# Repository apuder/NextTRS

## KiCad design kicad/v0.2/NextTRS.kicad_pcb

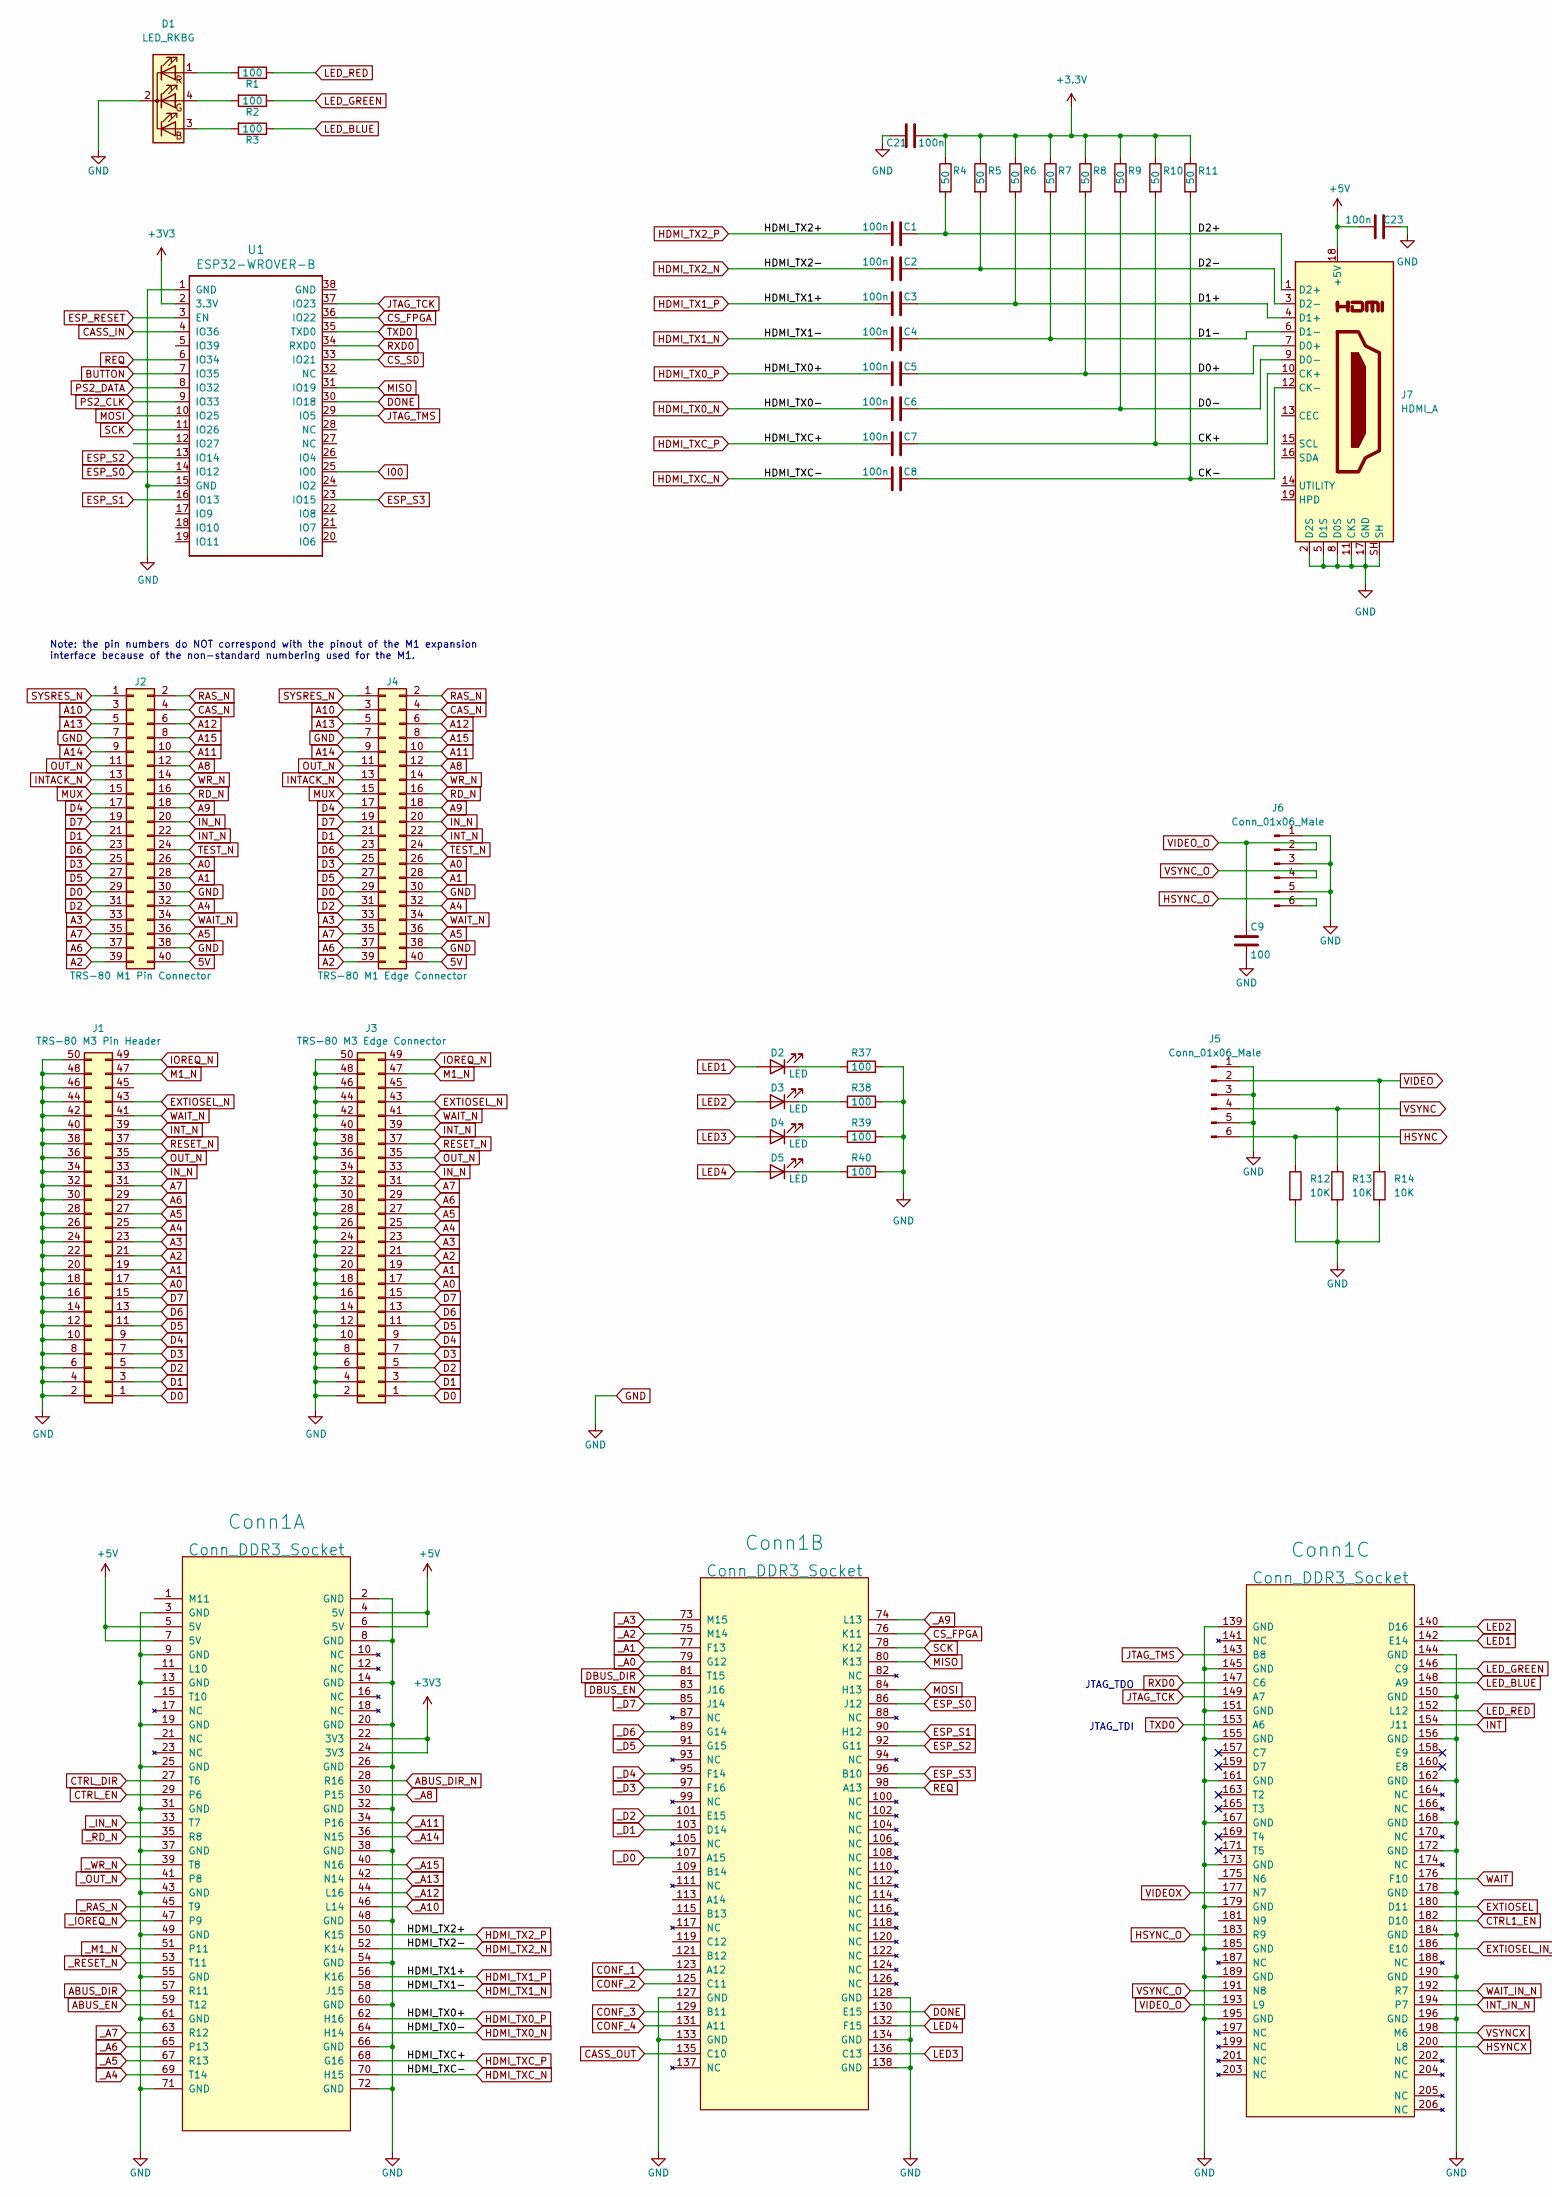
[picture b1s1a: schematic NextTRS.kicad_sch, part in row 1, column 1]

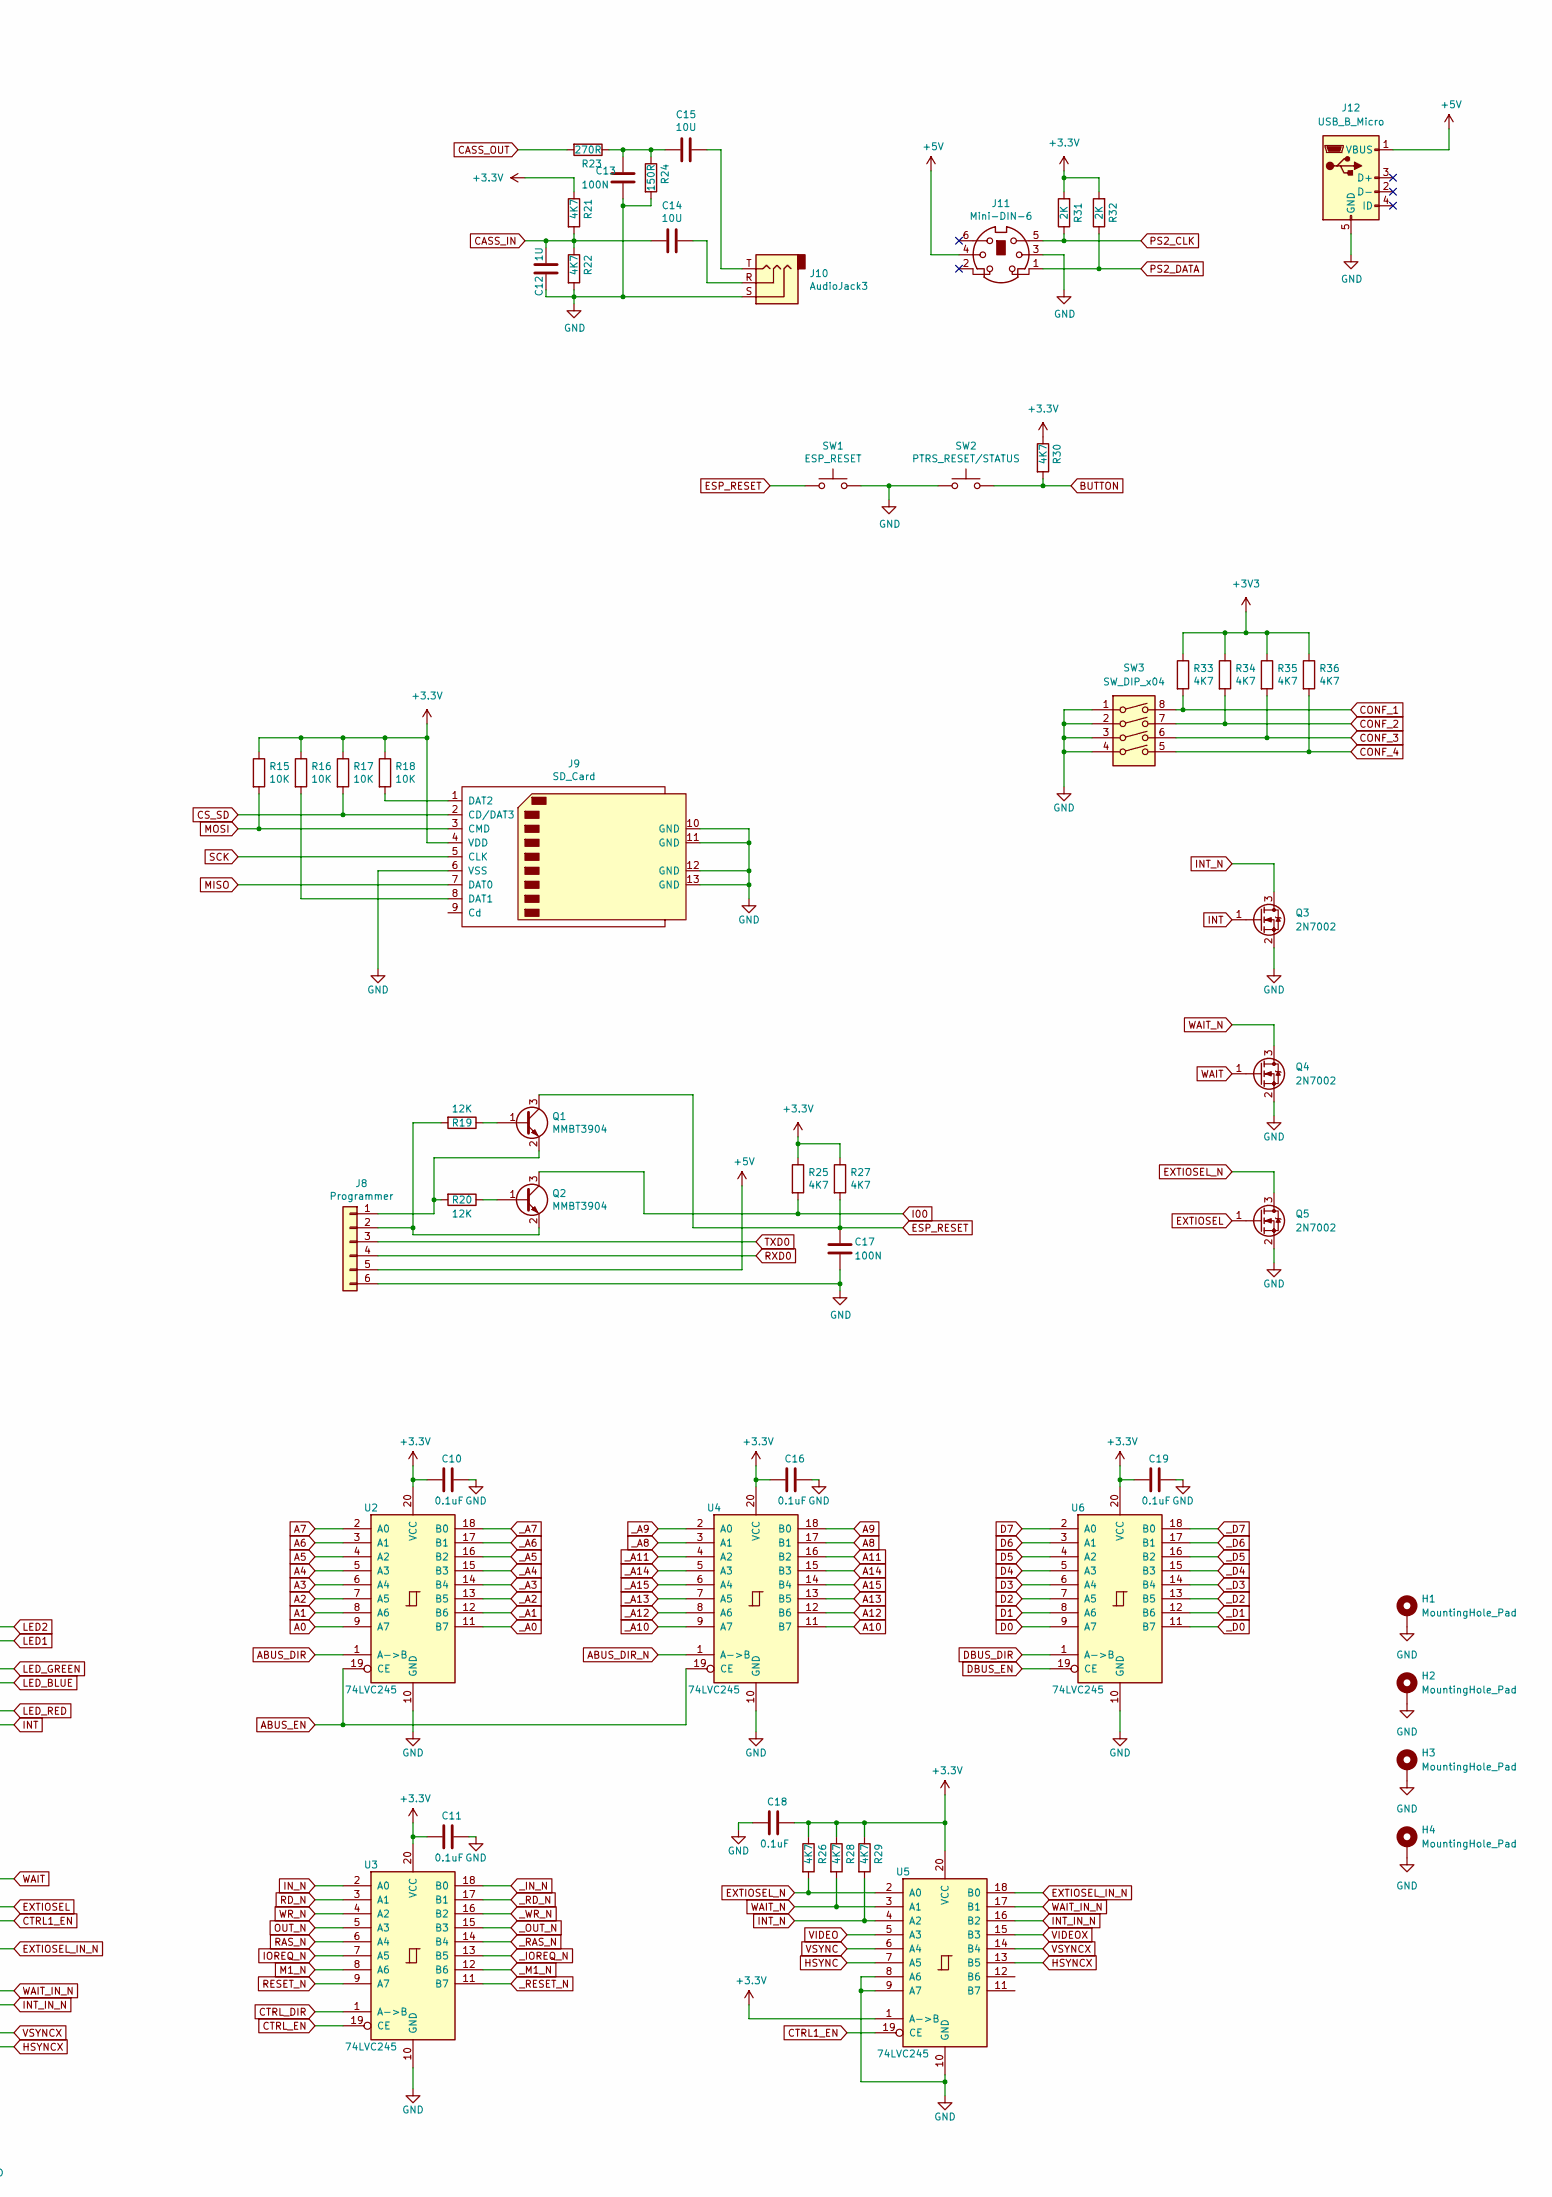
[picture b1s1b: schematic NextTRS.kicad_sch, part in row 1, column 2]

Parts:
C1, C2, C3, C4, C5, C6, C7, C8, C21, C23: 100n; C_0805_2012Metric_Pad1.18x1.45mm_HandSolder
C9: 100; C_0805_2012Metric_Pad1.18x1.45mm_HandSolder
C10, C11, C16, C18, C19: 0.1uF; C_0805_2012Metric_Pad1.18x1.45mm_HandSolder
C12: 1U; C_1206_3216Metric_Pad1.33x1.80mm_HandSolder
C13, C17: 100N; C_0805_2012Metric_Pad1.18x1.45mm_HandSolder
C14, C15: 10U; C_1206_3216Metric_Pad1.33x1.80mm_HandSolder
Conn1: Conn_DDR3_Socket; DDR3_socket
D1: LED_RKBG; LED_D5.0mm-4_RGB
D2, D3, D4, D5: LED; LED_0805_2012Metric_Pad1.15x1.40mm_HandSolder
H1, H2, H3, H4: MountingHole_Pad; MountingHole_3mm_Pad_Via
J1: TRS-80 M3 Pin Header; PinHeader_2x25_P2.54mm_Vertical
J2: TRS-80 M1 Pin Connector; PinHeader_2x20_P2.54mm_Vertical
J3: TRS-80 M3 Edge Connector; EDGE50
J4: TRS-80 M1 Edge Connector; TRSEDGE
J5, J6: Conn_01x06_Male; PinHeader_1x06_P2.54mm_Horizontal
J7: HDMI_A; HDMI_A_Molex_208658-1001_Horizontal
J8: Programmer; PinSocket_1x06_P2.54mm_Vertical
J9: SD_Card; TFP09-2-12B
J10: AudioJack3; Jack_3.5mm_CUI_SJ1-3535NG_Horizontal_CircularHoles
J11: Mini-DIN-6; minidin_6_ps2_pcb_mount
J12: USB_B_Micro; USBmicro-B
Q1, Q2: MMBT3904; SOT-23
Q3, Q4, Q5: 2N7002; SOT-23
R1, R2, R3, R37, R38, R39, R40: 100; R_0805_2012Metric_Pad1.20x1.40mm_HandSolder
R4, R5, R6, R7, R8, R9, R10, R11: 50; R_0805_2012Metric_Pad1.20x1.40mm_HandSolder
R12, R13, R14, R15, R16, R17, R18: 10K; R_0805_2012Metric_Pad1.20x1.40mm_HandSolder
R19, R20: 12K; R_0805_2012Metric_Pad1.20x1.40mm_HandSolder
R21, R22, R25, R26, R27, R28, R29, R30, R33, R34, R35, R36: 4K7; R_0805_2012Metric_Pad1.20x1.40mm_HandSolder
R23: 270R; R_0805_2012Metric_Pad1.20x1.40mm_HandSolder
R24: 150R; R_0805_2012Metric_Pad1.20x1.40mm_HandSolder
R31, R32: 2K; R_0805_2012Metric_Pad1.20x1.40mm_HandSolder
SW1: ESP_RESET; SW_PUSH_6mm
SW2: PTRS_RESET/STATUS; SW_PUSH_6mm
SW3: SW_DIP_x04; SW_DIP_SPSTx04_Slide_6.7x11.72mm_W8.61mm_P2.54mm_LowProfile
U1: ESP32-WROVER-B; ESP32-WROVER
U2, U3, U4, U5, U6: 74LVC245; SSOP-20_5.3x7.2mm_P0.65mm_slim

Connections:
5V: J2.40, J4.40
+5V: C23.1, Conn1.4 (5V), Conn1.5 (5V), Conn1.6 (5V), Conn1.7 (5V), J7.18 (+5V), J8.5, J11.4, J12.1 (VBUS)
/CK+: C7.2, J7.10 (CK+), R10.2
/CK-: C8.2, J7.12 (CK-), R11.2
/D0+: C5.2, J7.7 (D0+), R8.2
/D0-: C6.2, J7.9 (D0-), R9.2
/D1+: C3.2, J7.4 (D1+), R6.2
/D1-: C4.2, J7.6 (D1-), R7.2
/D2+: C1.2, J7.1 (D2+), R4.2
/D2-: C2.2, J7.3 (D2-), R5.2
A0: J1.17, J2.26, J3.17, J4.26, U2.9 (A7)
A1: J1.19, J2.28, J3.19, J4.28, U2.8 (A6)
A2: J1.21, J2.39, J3.21, J4.39, U2.7 (A5)
A3: J1.23, J2.33, J3.23, J4.33, U2.6 (A4)
A4: J1.25, J2.32, J3.25, J4.32, U2.5 (A3)
A5: J1.27, J2.36, J3.27, J4.36, U2.4 (A2)
A6: J1.29, J2.37, J3.29, J4.37, U2.3 (A1)
A7: J1.31, J2.35, J3.31, J4.35, U2.2 (A0)
A8: J2.12, J4.12, U4.17 (B1)
A9: J2.18, J4.18, U4.18 (B0)
A10: J2.3, J4.3, U4.11 (B7)
A11: J2.10, J4.10, U4.16 (B2)
A12: J2.6, J4.6, U4.12 (B6)
A13: J2.5, J4.5, U4.13 (B5)
A14: J2.9, J4.9, U4.15 (B3)
A15: J2.8, J4.8, U4.14 (B4)
ABUS_DIR: Conn1.57 (R11), U2.1 (A->B)
ABUS_DIR_N: Conn1.28 (R16), U4.1 (A->B)
ABUS_EN: Conn1.59 (T12), U2.19 (CE), U4.19 (CE)
BUTTON: R30.2, SW2.2, U1.7 (IO35)
CASS_IN: C12.1, C14.2, R21.2, R22.1, U1.4 (IO36)
CASS_OUT: Conn1.135 (C10), R23.2
CAS_N: J2.4, J4.4
CONF_1: Conn1.123 (A12), R33.2, SW3.8
CONF_2: Conn1.125 (C11), R34.2, SW3.7
CONF_3: Conn1.129 (B11), R35.2, SW3.6
CONF_4: Conn1.131 (A11), R36.2, SW3.5
CS_FPGA: Conn1.76 (K11), U1.36 (IO22)
CS_SD: J9.2 (CD/DAT3), R17.2, U1.33 (IO21)
CTRL1_EN: Conn1.182 (D10), U5.19 (CE)
CTRL_DIR: Conn1.27 (T6), U3.1 (A->B)
CTRL_EN: Conn1.29 (P6), U3.19 (CE)
D0: J1.1, J2.29, J3.1, J4.29, U6.9 (A7)
D1: J1.3, J2.21, J3.3, J4.21, U6.8 (A6)
D2: J1.5, J2.31, J3.5, J4.31, U6.7 (A5)
D3: J1.7, J2.25, J3.7, J4.25, U6.6 (A4)
D4: J1.9, J2.17, J3.9, J4.17, U6.5 (A3)
D5: J1.11, J2.27, J3.11, J4.27, U6.4 (A2)
D6: J1.13, J2.23, J3.13, J4.23, U6.3 (A1)
D7: J1.15, J2.19, J3.15, J4.19, U6.2 (A0)
DBUS_DIR: Conn1.81 (T15), U6.1 (A->B)
DBUS_EN: Conn1.83 (J16), U6.19 (CE)
DONE: Conn1.130 (E15), U1.30 (IO18)
ESP_RESET: C17.1, Q1.3 (C), R27.2, SW1.1, U1.3 (EN)
ESP_S0: Conn1.86 (J12), U1.14 (IO12)
ESP_S1: Conn1.90 (H12), U1.16 (IO13)
ESP_S2: Conn1.92 (G11), U1.13 (IO14)
ESP_S3: Conn1.96 (B10), U1.23 (IO15)
EXTIOSEL: Conn1.180 (D11), Q5.1 (G)
EXTIOSEL_IN_N: Conn1.186 (E10), U5.18 (B0)
EXTIOSEL_N: J1.43, J3.43, Q5.3 (D), R26.2, U5.2 (A0)
GND: C9.2, C10.1, C11.1, C12.2, C13.2, C16.1, C17.2, C18.2, C19.1, C21.2, C23.2, Conn1.2 (GND), Conn1.3 (GND), Conn1.8 (GND), Conn1.9 (GND), Conn1.13 (GND), Conn1.14 (GND), Conn1.19 (GND), Conn1.20 (GND), Conn1.25 (GND), Conn1.26 (GND), Conn1.31 (GND), Conn1.32 (GND), Conn1.37 (GND), Conn1.38 (GND), Conn1.43 (GND), Conn1.48 (GND), Conn1.49 (GND), Conn1.54 (GND), Conn1.55 (GND), Conn1.60 (GND), Conn1.61 (GND), Conn1.66 (GND), Conn1.71 (GND), Conn1.72 (GND), Conn1.127 (GND), Conn1.128 (GND), Conn1.133 (GND), Conn1.134 (GND), Conn1.138 (GND), Conn1.139 (GND), Conn1.144 (GND), Conn1.145 (GND), Conn1.150 (GND), Conn1.151 (GND), Conn1.155 (GND), Conn1.156 (GND), Conn1.161 (GND), Conn1.162 (GND), Conn1.167 (GND), Conn1.168 (GND), Conn1.172 (GND), Conn1.173 (GND), Conn1.178 (GND), Conn1.179 (GND), Conn1.184 (GND), Conn1.185 (GND), Conn1.189 (GND), Conn1.190 (GND), Conn1.195 (GND), Conn1.196 (GND), D1.2 (K), H1.1, H2.1, H3.1, H4.1, J1.2, J1.4, J1.6, J1.8, J1.10, J1.12, J1.14, J1.16, J1.18, J1.20, J1.22, J1.24, J1.26, J1.28, J1.30, J1.32, J1.34, J1.36, J1.38, J1.40, J1.42, J1.44, J1.46, J1.48, J1.50, J2.7, J2.30, J2.38, J3.2, J3.4, J3.6, J3.8, J3.10, J3.12, J3.14, J3.16, J3.18, J3.20, J3.22, J3.24, J3.26, J3.28, J3.30, J3.32, J3.34, J3.36, J3.38, J3.40, J3.42, J3.44, J3.46, J3.48, J3.50, J4.7, J4.30, J4.38, J5.1, J5.3, J5.5, J6.1, J6.3, J6.5, J7.2 (D2S), J7.5 (D1S), J7.8 (D0S), J7.11 (CKS), J7.17 (GND), J7.SH, J8.6, J9.6 (VSS), J9.10 (GND), J9.11 (GND), J9.12 (GND), J9.13 (GND), J10.S, J11.3, J12.5 (GND), Q3.2 (S), Q4.2 (S), Q5.2 (S), R12.2, R13.2, R14.2, R22.2, R24.2, R37.2, R38.2, R39.2, R40.2, SW1.2, SW2.1, SW3.1, SW3.2, SW3.3, SW3.4, U1.1 (GND), U1.15 (GND), U2.10 (GND), U3.10 (GND), U4.10 (GND), U5.8 (A6), U5.9 (A7), U5.10 (GND), U6.10 (GND)
HDMI_TX0_N: C6.1, Conn1.64 (H14)
HDMI_TX0_P: C5.1, Conn1.62 (H16)
HDMI_TX1_N: C4.1, Conn1.58 (J15)
HDMI_TX1_P: C3.1, Conn1.56 (K16)
HDMI_TX2_N: C2.1, Conn1.52 (K14)
HDMI_TX2_P: C1.1, Conn1.50 (K15)
HDMI_TXC_N: C8.1, Conn1.70 (H15)
HDMI_TXC_P: C7.1, Conn1.68 (G16)
HSYNC: J5.6, R12.1, U5.7 (A5)
HSYNCX: Conn1.200 (L8), U5.13 (B5)
HSYNC_O: Conn1.183 (R9), J6.6
I00: Q2.3 (C), R25.2, U1.25 (IO0)
INT: Conn1.154 (J11), Q3.1 (G)
INTACK_N: J2.13, J4.13
INT_IN_N: Conn1.194 (P7), U5.16 (B2)
INT_N: J1.39, J2.22, J3.39, J4.22, Q3.3 (D), R29.2, U5.4 (A2)
IN_N: J1.33, J2.20, J3.33, J4.20, U3.2 (A0)
IOREQ_N: J1.49, J3.49, U3.7 (A5)
JTAG_TCK: Conn1.149 (A7), U1.37 (IO23)
JTAG_TMS: Conn1.143 (B8), U1.29 (IO5)
LED1: Conn1.142 (E14), D2.2 (A)
LED2: Conn1.140 (D16), D3.2 (A)
LED3: Conn1.136 (C13), D4.2 (A)
LED4: Conn1.132 (F15), D5.2 (A)
LED_BLUE: Conn1.148 (A9), R3.1
LED_GREEN: Conn1.146 (C9), R2.1
LED_RED: Conn1.152 (L12), R1.1
M1_N: J1.47, J3.47, U3.8 (A6)
MISO: Conn1.80 (K13), J9.7 (DAT0), U1.31 (IO19)
MOSI: Conn1.84 (H13), J9.3 (CMD), R15.2, U1.10 (IO25)
MUX: J2.15, J4.15
unnamed: C13.1, C15.2, R23.1, R24.1
unnamed: C14.1, J10.R
unnamed: C15.1, J10.T
unnamed: D1.1 (RA), R1.2
unnamed: D1.3 (BA), R3.2
unnamed: D1.4 (GA), R2.2
unnamed: D2.1 (K), R37.1
unnamed: D3.1 (K), R38.1
unnamed: D4.1 (K), R39.1
unnamed: D5.1 (K), R40.1
unnamed: J8.1, Q1.2 (E), R20.2
unnamed: J8.2, Q2.2 (E), R19.2
unnamed: J9.1 (DAT2), R18.2
unnamed: J9.8 (DAT1), R16.2
unnamed: Q1.1 (B), R19.1
unnamed: Q2.1 (B), R20.1
OUT_N: J1.35, J2.11, J3.35, J4.11, U3.5 (A3)
PS2_CLK: J11.5, R31.1, U1.9 (IO33)
PS2_DATA: J11.1, R32.1, U1.8 (IO32)
RAS_N: J2.2, J4.2, U3.6 (A4)
RD_N: J2.16, J4.16, U3.3 (A1)
REQ: Conn1.98 (A13), U1.6 (IO34)
RESET_N: J1.37, J3.37, U3.9 (A7)
RXD0: Conn1.147 (C6), J8.4, U1.34 (RXD0)
SCK: Conn1.78 (K12), J9.5 (CLK), U1.11 (IO26)
SYSRES_N: J2.1, J4.1
TEST_N: J2.24, J4.24
TXD0: Conn1.153 (A6), J8.3, U1.35 (TXD0)
VIDEO: J5.2, R14.1, U5.5 (A3)
VIDEOX: Conn1.177 (N7), U5.15 (B3)
VIDEO_O: C9.1, Conn1.193 (L9), J6.2
VSYNC: J5.4, R13.1, U5.6 (A4)
VSYNCX: Conn1.198 (M6), U5.14 (B4)
VSYNC_O: Conn1.191 (N8), J6.4
WAIT: Conn1.176 (F10), Q4.1 (G)
WAIT_IN_N: Conn1.192 (R7), U5.17 (B1)
WAIT_N: J1.41, J2.34, J3.41, J4.34, Q4.3 (D), R28.2, U5.3 (A1)
WR_N: J2.14, J4.14, U3.4 (A2)
_A0: Conn1.79 (G12), U2.11 (B7)
_A1: Conn1.77 (F13), U2.12 (B6)
_A2: Conn1.75 (M14), U2.13 (B5)
_A3: Conn1.73 (M15), U2.14 (B4)
_A4: Conn1.69 (T14), U2.15 (B3)
_A5: Conn1.67 (R13), U2.16 (B2)
_A6: Conn1.65 (P13), U2.17 (B1)
_A7: Conn1.63 (R12), U2.18 (B0)
_A8: Conn1.30 (P15), U4.3 (A1)
_A9: Conn1.74 (L13), U4.2 (A0)
_A10: Conn1.46 (L14), U4.9 (A7)
_A11: Conn1.34 (P16), U4.4 (A2)
_A12: Conn1.44 (L16), U4.8 (A6)
_A13: Conn1.42 (N14), U4.7 (A5)
_A14: Conn1.36 (N15), U4.5 (A3)
_A15: Conn1.40 (N16), U4.6 (A4)
_D0: Conn1.107 (A15), U6.11 (B7)
_D1: Conn1.103 (D14), U6.12 (B6)
_D2: Conn1.101 (E15), U6.13 (B5)
_D3: Conn1.97 (F16), U6.14 (B4)
_D4: Conn1.95 (F14), U6.15 (B3)
_D5: Conn1.91 (G15), U6.16 (B2)
_D6: Conn1.89 (G14), U6.17 (B1)
_D7: Conn1.85 (J14), U6.18 (B0)
_IN_N: Conn1.33 (T7), U3.18 (B0)
_IOREQ_N: Conn1.47 (P9), U3.13 (B5)
_M1_N: Conn1.51 (P11), U3.12 (B6)
_OUT_N: Conn1.41 (P8), U3.15 (B3)
_RAS_N: Conn1.45 (T9), U3.14 (B4)
_RD_N: Conn1.35 (R8), U3.17 (B1)
_RESET_N: Conn1.53 (T11), U3.11 (B7)
_WR_N: Conn1.39 (T8), U3.16 (B2)

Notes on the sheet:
JTAG_TDO
Note: the pin numbers do NOT correspond with the pinout of the M1 expansion interface because of the non-standard numbering used for the M1.
JTAG_TDI

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
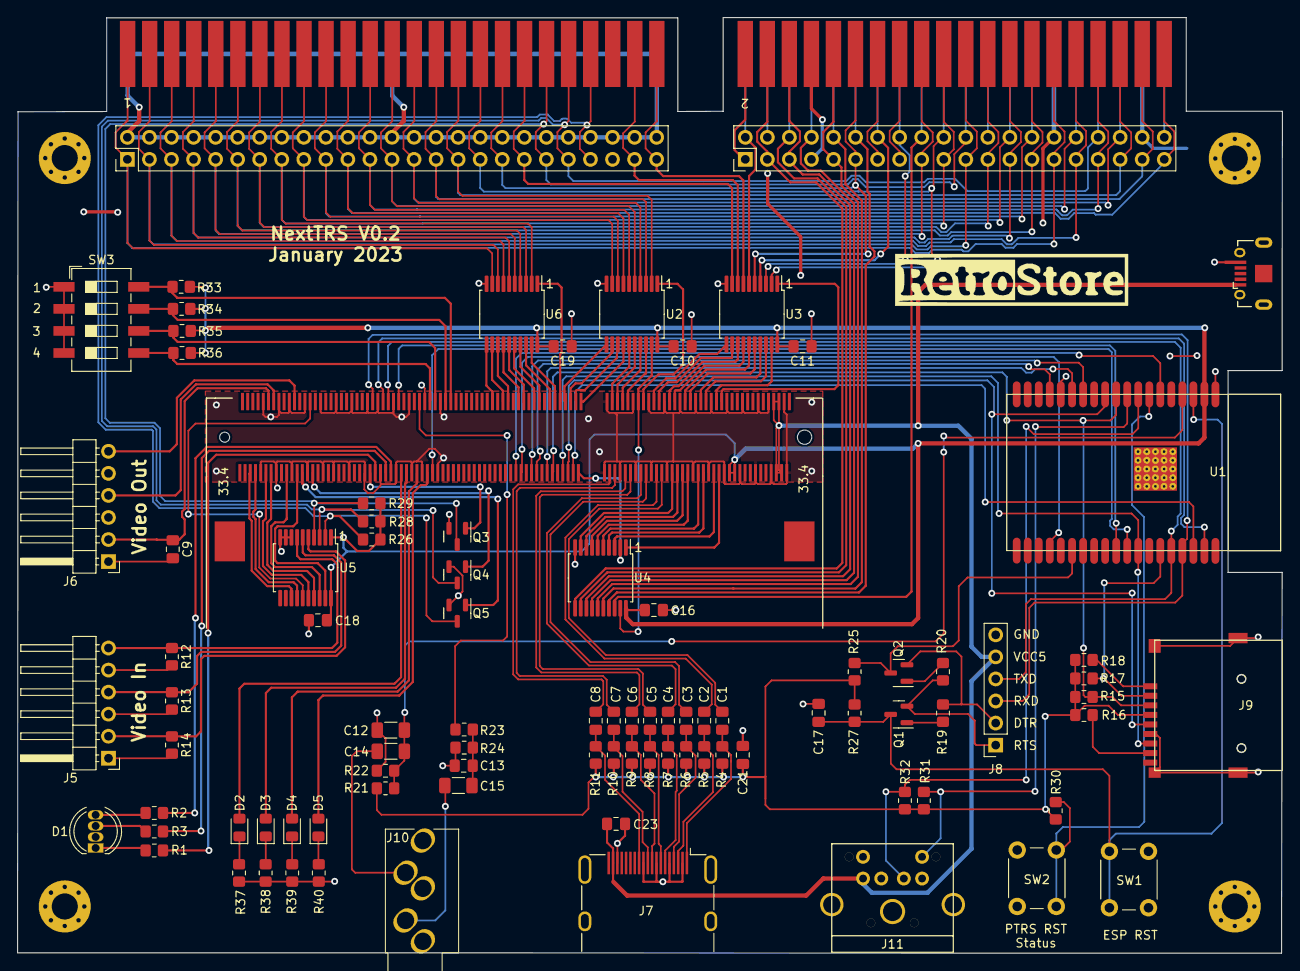
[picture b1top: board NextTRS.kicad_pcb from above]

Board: 2 copper layers, 145.7 x 107.8 mm, 98 parts (0 on the bottom side), 165 nets.

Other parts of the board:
G1: LOGO

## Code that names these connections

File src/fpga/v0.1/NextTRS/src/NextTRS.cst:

//Copyright (C)2014-2022 Gowin Semiconductor Corporation.
//All rights reserved. 
//File Title: Physical Constraints file
//GOWIN Version: 1.9.8.09
//Part Number: GW2A-LV18PG256C8/I7
//Device: GW2A-18C
//Created Time: Tue 12 27 23:20:03 2022

IO_LOC "CTRL1_EN" D10;
IO_PORT "CTRL1_EN" PULL_MODE=UP DRIVE=8;
IO_LOC "EXTIOSEL" D11;
IO_PORT "EXTIOSEL" PULL_MODE=UP DRIVE=8;
IO_LOC "WAIT" F10;
IO_PORT "WAIT" PULL_MODE=UP DRIVE=8;
IO_LOC "INT" J11;
IO_PORT "INT" PULL_MODE=UP DRIVE=8;
IO_LOC "LED_BLUE" A9;
IO_PORT "LED_BLUE" PULL_MODE=UP DRIVE=8;
IO_LOC "LED_RED" L12;
IO_PORT "LED_RED" PULL_MODE=UP DRIVE=8;
IO_LOC "LED_GREEN" C9;
IO_PORT "LED_GREEN" PULL_MODE=UP DRIVE=8;
IO_LOC "VIDEO_O" L9;
IO_PORT "VIDEO_O" PULL_MODE=UP DRIVE=8;
IO_LOC "VSYNC_O" N8;
IO_PORT "VSYNC_O" PULL_MODE=UP DRIVE=8;
IO_LOC "HSYNC_O" R9;
IO_PORT "HSYNC_O" PULL_MODE=UP DRIVE=8;
IO_LOC "LED[3]" F15;
IO_PORT "LED[3]" PULL_MODE=UP DRIVE=8;
IO_LOC "LED[2]" C13;
IO_PORT "LED[2]" PULL_MODE=UP DRIVE=8;
IO_LOC "LED[1]" D16;
IO_PORT "LED[1]" PULL_MODE=UP DRIVE=8;
IO_LOC "LED[0]" E14;
IO_PORT "LED[0]" PULL_MODE=UP DRIVE=8;
IO_LOC "REQ" A13;
IO_PORT "REQ" PULL_MODE=UP DRIVE=8;
IO_LOC "ESP_S[3]" B10;
IO_PORT "ESP_S[3]" PULL_MODE=UP DRIVE=8;
IO_LOC "ESP_S[2]" G11;
IO_PORT "ESP_S[2]" PULL_MODE=UP DRIVE=8;
IO_LOC "ESP_S[1]" H12;
IO_PORT "ESP_S[1]" PULL_MODE=UP DRIVE=8;
IO_LOC "ESP_S[0]" J12;
IO_PORT "ESP_S[0]" PULL_MODE=UP DRIVE=8;
IO_LOC "MISO" K13;
IO_PORT "MISO" PULL_MODE=UP DRIVE=8;
IO_LOC "CASS_OUT" C10;
IO_PORT "CASS_OUT" PULL_MODE=UP DRIVE=8;
IO_LOC "DBUS_EN" J16;
IO_PORT "DBUS_EN" PULL_MODE=UP DRIVE=8;
IO_LOC "DBUS_DIR" T15;
IO_PORT "DBUS_DIR" PULL_MODE=UP DRIVE=8;
IO_LOC "HDMI_TXC_N" H15;
IO_PORT "HDMI_TXC_N" PULL_MODE=UP DRIVE=8;
IO_LOC "HDMI_TXC_P" G16;
IO_PORT "HDMI_TXC_P" PULL_MODE=UP DRIVE=8;
IO_LOC "HDMI_TX_N[2]" K14;
IO_PORT "HDMI_TX_N[2]" PULL_MODE=UP DRIVE=8;
IO_LOC "HDMI_TX_N[1]" J15;
IO_PORT "HDMI_TX_N[1]" PULL_MODE=UP DRIVE=8;
IO_LOC "HDMI_TX_N[0]" H14;
IO_PORT "HDMI_TX_N[0]" PULL_MODE=UP DRIVE=8;
IO_LOC "HDMI_TX_P[2]" K15;
IO_PORT "HDMI_TX_P[2]" PULL_MODE=UP DRIVE=8;
IO_LOC "HDMI_TX_P[1]" K16;
IO_PORT "HDMI_TX_P[1]" PULL_MODE=UP DRIVE=8;
IO_LOC "HDMI_TX_P[0]" H16;
IO_PORT "HDMI_TX_P[0]" PULL_MODE=UP DRIVE=8;
IO_LOC "ABUS_DIR_N" R16;
IO_PORT "ABUS_DIR_N" PULL_MODE=UP DRIVE=8;
IO_LOC "ABUS_EN" T12;
IO_PORT "ABUS_EN" PULL_MODE=UP DRIVE=8;
IO_LOC "ABUS_DIR" R11;
IO_PORT "ABUS_DIR" PULL_MODE=UP DRIVE=8;
IO_LOC "CTRL_EN" P6;
IO_PORT "CTRL_EN" PULL_MODE=UP DRIVE=8;
IO_LOC "CTRL_DIR" T6;
IO_PORT "CTRL_DIR" PULL_MODE=UP DRIVE=8;
IO_LOC "EXTIOSEL_IN_N" E10;
IO_PORT "EXTIOSEL_IN_N" PULL_MODE=UP;
IO_LOC "VIDEOX" N7;
IO_PORT "VIDEOX" PULL_MODE=UP;
IO_LOC "clk_in" H11;
IO_PORT "clk_in" PULL_MODE=UP;
IO_LOC "SCK" K12;
IO_PORT "SCK" PULL_MODE=UP;
IO_LOC "DONE" E16;
IO_PORT "DONE" PULL_MODE=UP;
IO_LOC "CS_FPGA" K11;
IO_PORT "CS_FPGA" PULL_MODE=UP;
IO_LOC "VSYNCX" M6;
IO_PORT "VSYNCX" PULL_MODE=UP;
IO_LOC "_WR_N" T8;
IO_PORT "_WR_N" PULL_MODE=UP DRIVE=8;
IO_LOC "CONF[2]" B11;
IO_PORT "CONF[2]" PULL_MODE=UP;
IO_LOC "CONF[0]" A12;
IO_PORT "CONF[0]" PULL_MODE=UP;
IO_LOC "_RD_N" R8;
IO_PORT "_RD_N" PULL_MODE=UP DRIVE=8;
IO_LOC "MOSI" H13;
IO_PORT "MOSI" PULL_MODE=UP;
IO_LOC "HSYNCX" L8;
IO_PORT "HSYNCX" PULL_MODE=UP;
IO_LOC "CONF[3]" A11;
IO_PORT "CONF[3]" PULL_MODE=UP;
IO_LOC "CONF[1]" C11;
IO_PORT "CONF[1]" PULL_MODE=UP;
IO_LOC "_IN_N" T7;
IO_PORT "_IN_N" PULL_MODE=UP DRIVE=8;
IO_LOC "WAIT_IN_N" R7;
IO_PORT "WAIT_IN_N" PULL_MODE=UP;
IO_LOC "_A[4]" T14;
IO_PORT "_A[4]" PULL_MODE=UP DRIVE=8;
IO_LOC "_A[3]" M15;
IO_PORT "_A[3]" PULL_MODE=UP DRIVE=8;
IO_LOC "_A[2]" M14;
IO_PORT "_A[2]" PULL_MODE=UP DRIVE=8;
IO_LOC "_M1_N" P11;
IO_PORT "_M1_N" PULL_MODE=UP DRIVE=8;
IO_LOC "_RAS_N" T9;
IO_PORT "_RAS_N" PULL_MODE=UP DRIVE=8;
IO_LOC "_OUT_N" P8;
IO_PORT "_OUT_N" PULL_MODE=UP DRIVE=8;
IO_LOC "_A[10]" L14;
IO_PORT "_A[10]" PULL_MODE=UP DRIVE=8;
IO_LOC "_A[13]" N14;
IO_PORT "_A[13]" PULL_MODE=UP DRIVE=8;
IO_LOC "_A[11]" P16;
IO_PORT "_A[11]" PULL_MODE=UP DRIVE=8;
IO_LOC "_IOREQ_N" P9;
IO_PORT "_IOREQ_N" PULL_MODE=UP DRIVE=8;
IO_LOC "_A[0]" G12;
IO_PORT "_A[0]" PULL_MODE=UP DRIVE=8;
IO_LOC "_D[0]" A15;
IO_PORT "_D[0]" PULL_MODE=UP DRIVE=8;
IO_LOC "_A[15]" N16;
IO_PORT "_A[15]" PULL_MODE=UP DRIVE=8;
IO_LOC "_RESET_N" T11;
IO_PORT "_RESET_N" PULL_MODE=UP DRIVE=8;
IO_LOC "_A[14]" N15;
IO_PORT "_A[14]" PULL_MODE=UP DRIVE=8;
IO_LOC "_A[12]" L16;
IO_PORT "_A[12]" PULL_MODE=UP DRIVE=8;
IO_LOC "_A[9]" L13;
IO_PORT "_A[9]" PULL_MODE=UP DRIVE=8;
IO_LOC "_A[8]" P15;
IO_PORT "_A[8]" PULL_MODE=UP DRIVE=8;
IO_LOC "_A[7]" R12;
IO_PORT "_A[7]" PULL_MODE=UP DRIVE=8;
IO_LOC "_A[6]" P13;
IO_PORT "_A[6]" PULL_MODE=UP DRIVE=8;
IO_LOC "_A[1]" F13;
IO_PORT "_A[1]" PULL_MODE=UP DRIVE=8;
IO_LOC "_A[5]" R13;
IO_PORT "_A[5]" PULL_MODE=UP DRIVE=8;
IO_LOC "_D[7]" J14;
IO_PORT "_D[7]" PULL_MODE=UP DRIVE=8;
IO_LOC "_D[4]" F14;
IO_PORT "_D[4]" PULL_MODE=UP DRIVE=8;
IO_LOC "_D[2]" E15;
IO_PORT "_D[2]" PULL_MODE=UP DRIVE=8;
IO_LOC "_D[1]" D14;
IO_PORT "_D[1]" PULL_MODE=UP DRIVE=8;
IO_LOC "_D[5]" G15;
IO_PORT "_D[5]" PULL_MODE=UP DRIVE=8;
IO_LOC "_D[6]" G14;
IO_PORT "_D[6]" PULL_MODE=UP DRIVE=8;
IO_LOC "_D[3]" F16;
IO_PORT "_D[3]" PULL_MODE=UP DRIVE=8;

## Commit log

2022-12-07 Initial version
2022-12-09 Do not use Bank 4 (1.5V)
2022-12-09 Add hires interface for the M3
2022-12-13 Add HDMI connector
2022-12-13 HDMI: move resistors before caps
2022-12-16 Move LED to FPGA. Add JTAG interface
2022-12-26 Updated schematics to facilitate routing
2022-12-26 Add remaining traces
2022-12-27 Added HDMI shield grounds. Added ground pour under Nano socket. Correced U5 connections.
2022-12-27 Moved HDMI termination Rs. Added HDMI shield grounds.
2022-12-27 New routing for U5
2022-12-28 Stiffened grounds around TRS-80 connectors.
2022-12-28 Fixed clearance violation.
2022-12-28 Move micro-USB connector closer to edge
2022-12-28 Generate Gerber files
2022-12-28 Add FPGA constraints
2023-01-18 Several PCB updates
    Reduce width of SOP pads
    Move U4 to the left to avoid collision with 20K components
    Swapped pins of M1 edge connector
    Make HDMI traces equal length
2023-01-27 Ported TRS-IO-M1 FPGA code to NextTRS
